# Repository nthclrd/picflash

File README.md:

# picflash

Programmeur PIC open source en Rust, pour remplacer MPLAB IPE. Il pilote une
carte maison à RP2040 (prototype sur Pi Pico en attendant le PCB) ou un PICkit
4, PICkit 5, PICkit Basic ou MPLAB Snap. Il assemble, programme et désassemble
sans MPLAB X ni XC8.

**État :** testé seulement sur un PIC simulé. Ni le PICkit, ni la carte, ni le
firmware n'ont tourné sur du vrai matériel ; la carte (`hardware/`) n'a pas été
fabriquée. Développé avec l'aide de Claude (Anthropic).

## Installer

| Système | Fichier | Remarque |
|---------|---------|----------|
| macOS   | `.dmg`  | 1er lancement : clic droit > Ouvrir (app non signée) |
| Windows | `-setup.exe` | SmartScreen : « Exécuter quand même » |
| Linux   | `.deb` ou `.AppImage` | le `.deb` installe la règle udev |

Dans la fenêtre : déposer un `.asm` ou un `.hex`, puis « Programmer ».
En ligne de commande : `cargo install --path host`.

## Utiliser

```sh
picflash asm blink.asm               # -> blink.hex
picflash write blink.hex             # efface, écrit, vérifie, lance
picflash read dump.hex
picflash -P16F1789 disasm blink.hex
picflash --tool pickit --power 3.3 id
picflash parts                       # puces supportées
picflash-ipecmd -TPSIM -E -M -P16F1789 -Fblink.hex -OL   # mêmes options qu'ipecmd
```

`-TPSIM` (ou « Simulateur » dans la fenêtre) fait tout sur un PIC simulé, sans
matériel. L'onglet « Débogueur » exécute le programme pas à pas sur ce
simulateur (sans périphériques).

Dans le `Makefile` du labo, remplacer `ipecmd` par `picflash-ipecmd` :

```make
IPECMD ?= $(HOME)/.cargo/bin/picflash-ipecmd
```

## Programmateurs

| Outil | Basse tension (LVP) | Haute tension (VPP) | Alimente la cible |
|-------|:--:|:--:|:--:|
| carte picflash | oui | oui | 1,5-4,8 V |
| prototype Pi Pico | oui | non | non |
| PICkit 4 / 5 | oui | oui | oui |
| PICkit Basic, Snap | oui | non | non |

Les outils Microchip doivent être en mode MPLAB. Windows : pilote WinUSB
installé par MPLAB X. Détails du protocole : `docs/pickit-gen4.md`.

## Puces supportées

201 PIC16 enhanced mid-range (familles PIC16F1xxx et PIC16F18xxx), décrites par
la base `host/data/devices.json.gz` extraite des device packs Microchip
(Apache-2.0). Une spec de programmation n'est ajoutée que si toutes ses puces
suivent exactement la même séquence (`SPECS` dans `host/src/device.rs`).

## Assembleur

`picflash asm` accepte les sources `pic-as` (XC8) pour PIC16 enhanced :
directives, macros, `PSECT`, `CONFIG`, `#include <xc.inc>`. Vérifié contre
`pic-as` v3.10 sur le `blink.asm` du labo et 400 programmes aléatoires : même
`.hex`, mêmes erreurs. Non supporté : PIC18, PIC10/12, plusieurs fichiers
liés, `IRP`, labels temporaires.

## Câblage du prototype Pi Pico

| Pico | PIC16F1789 (PDIP-40) | ICSP |
|------|----------------------|------|
| GP4 | MCLR (1) | 1 |
| 3V3(OUT) | VDD (11, 32) | 2 |
| GND | VSS (12, 31) | 3 |
| GP3 | ICSPDAT (40) | 4 |
| GP2 | ICSPCLK (39) | 5 |

Cible en 3,3 V. Garder `CONFIG LVP = ON` : `picflash write` refuse sinon.

Firmware : brancher en maintenant BOOTSEL, copier `picflash-firmware-pico.uf2`
(ou `picflash-firmware.uf2` pour la carte) sur le disque RPI-RP2.

## Structure

| Dossier | Rôle |
|---------|------|
| `host/` | CLI, assembleur, simulateur, programmation |
| `gui/` | interface |
| `protocol/` | protocole USB partagé hôte/firmware |
| `firmware/` | RP2040 : exécute les séquences bit à bit envoyées par l'hôte |
| `hardware/` | carte KiCad et fichiers JLCPCB |

Toute la logique PIC est côté PC : une nouvelle famille ne demande pas de
reflasher la carte.

## Tests

```sh
cargo test
```

Le PIC simulé décode chaque front d'horloge comme la vraie puce ; les tests
échouent si une séquence est fausse (ordre des bits, attente oubliée…). Ça ne
remplace pas un essai sur vraie puce.

## Licence

MIT (`LICENSE`). Données de puces (`host/data/`) : Apache-2.0, Microchip.

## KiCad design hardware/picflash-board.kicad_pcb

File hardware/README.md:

# Carte picflash (RP2040)

Design original tiré des datasheets publiques (RP2040, MT3608, TLV758,
SN74LVC1T45). **Non testé, à relire avant fabrication.**

## Générer

Le schéma et le PCB sont générés par les scripts de `tools/` : la netlist
Python (`tools/gen_schematic.py`) est la source de vérité.

```sh
make all FREEROUTING=/chemin/freerouting-2.4.1.jar
```

Étapes : schéma généré et vérifié net par net, placement, routage automatique
(Freerouting), plans de masse, ERC/DRC (0 erreur), puis `fab/` : Gerber,
perçages, BOM et CPL au format JLCPCB. Chaque pièce de la BOM a un numéro LCSC
(stock vérifié le 15/10/2026, à revérifier à la commande).

Carte 72 × 44 mm, 4 couches (In1 masse, In2 +3,3 V), composants sur une face.

## Blocs

| Bloc | Composants | Rôle |
|------|------------|------|
| USB | J1 USB-C, U2 USBLC6, F1 | alimentation 5 V, données protégées |
| 3,3 V | U3 AP2112K | logique |
| MCU | U1 RP2040, U4 flash, Y1 12 MHz | |
| Lignes ICSP | U5-U9 SN74LVC1T45 | adaptation 1,65-5,5 V, haute impédance au démarrage |
| VPP | U11 MT3608 | 6,7-13,9 V, réglé par PWM, mesuré sur ADC1 |
| VDD cible | U12 TLV75801 | 1,5-4,86 V, réglé par PWM, mesuré sur ADC0 |
| MCLR | Q1, U10 + D5, Q3 | VPP, niveau VDD ou masse |
| Connecteur | J2 8 broches | brochage PICkit 4/5 |

Brochage GPIO : `firmware/src/hw_board.rs`.

## Règles pour le firmware

- Ne jamais activer VPP_ON et MCLR_PD en même temps.
- PWM à 0 = tension max (13,9 V pour VPP) : fixer le PWM avant d'activer le
  régulateur.
- Avant d'alimenter la cible, vérifier sur ADC0 qu'aucune alimentation
  externe n'est présente.

## Avant de commander

- Relire le routage automatique : masse sous l'USB, boucle du MT3608, pistes
  VPP/MCLR.
- Vérifier les rotations du CPL dans l'aperçu JLCPCB.
- Valeurs à valider sur la première carte : self 22 µH, stabilité des
  régulateurs avec l'injection PWM.
- J2 est traversant : assemblage THT ou soudure à la main.

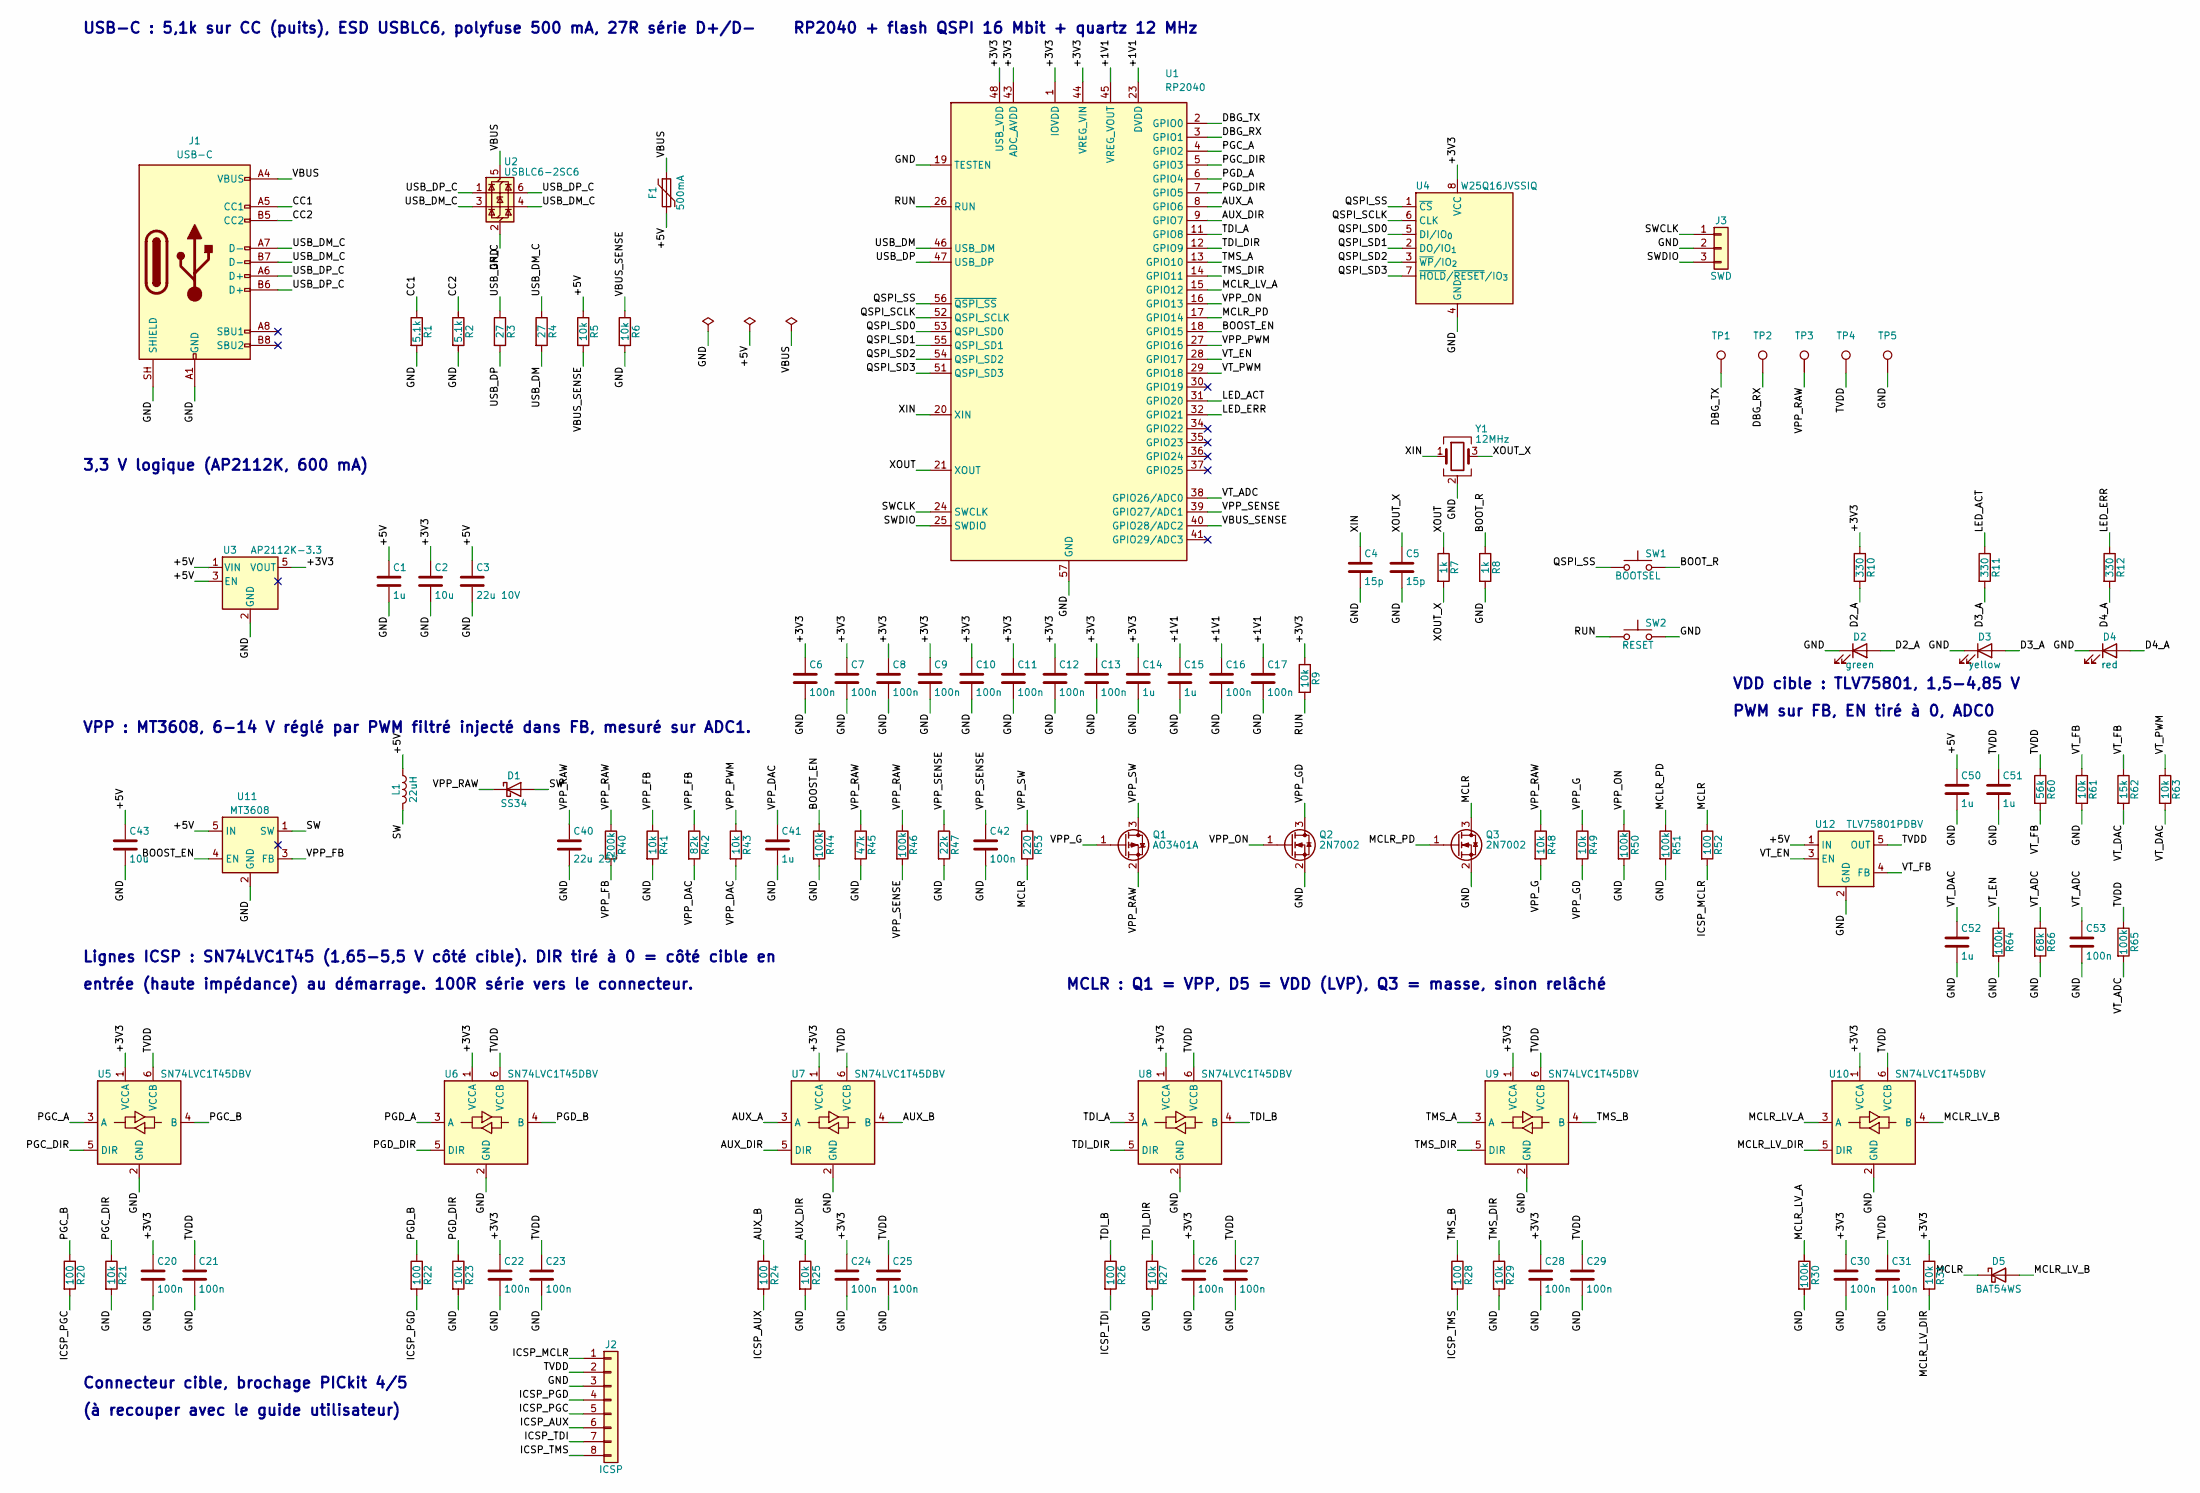
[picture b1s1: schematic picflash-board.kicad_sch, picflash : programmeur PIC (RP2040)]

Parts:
C1, C14, C15, C41, C50, C51, C52: 1u; C_0603_1608Metric; LCSC C15849
C2, C43: 10u; C_0805_2012Metric; LCSC C15850
C3: 22u 10V; C_0805_2012Metric; LCSC C45783
C4, C5: 15p; C_0603_1608Metric; LCSC C1644
C6, C7, C8, C9, C10, C11, C12, C13, C16, C17, C20, C21, C22, C23, C24, C25, C26, C27, C28, C29, C30, C31, C42, C53: 100n; C_0603_1608Metric; LCSC C14663
C40: 22u 25V; C_1206_3216Metric; LCSC C12891
D1: SS34; D_SMA; LCSC C8678
D2: green; LED_0603_1608Metric; LCSC C12624
D3: yellow; LED_0603_1608Metric; LCSC C2287
D4: red; LED_0603_1608Metric; LCSC C2286
D5: BAT54WS; D_SOD-323; LCSC C7502694
F1: 500mA; Fuse_1206_3216Metric; LCSC C720075
J1: USB-C; USB_C_Receptacle_HRO_TYPE-C-31-M-12; LCSC C165948
J2: ICSP; PinSocket_1x08_P2.54mm_Horizontal; LCSC C22436149
J3: SWD; PinHeader_1x03_P1.27mm_Vertical; LCSC C22438100
L1: 22uH; L_Cenker_CKCS4030; LCSC C354592
Q1: AO3401A; SOT-23; LCSC C15127
Q2, Q3: 2N7002; SOT-23; LCSC C8545
R1, R2: 5.1k; R_0603_1608Metric; LCSC C23186
R3, R4: 27; R_0603_1608Metric; LCSC C25190
R5, R6, R9, R21, R23, R25, R27, R29, R31, R41, R43, R48, R49, R61, R63: 10k; R_0603_1608Metric; LCSC C25804
R7, R8: 1k; R_0603_1608Metric; LCSC C21190
R10, R11, R12: 330; R_0603_1608Metric; LCSC C23138
R20, R22, R24, R26, R28, R52: 100; R_0603_1608Metric; LCSC C22775
R30, R44, R46, R50, R51, R64, R65: 100k; R_0603_1608Metric; LCSC C25803
R40: 200k; R_0603_1608Metric; LCSC C25811
R42: 82k; R_0603_1608Metric; LCSC C23254
R45: 47k; R_0603_1608Metric; LCSC C25819
R47: 22k; R_0603_1608Metric; LCSC C31850
R53: 220; R_0603_1608Metric; LCSC C22962
R60: 56k; R_0603_1608Metric; LCSC C23206
R62: 15k; R_0603_1608Metric; LCSC C22809
R66: 68k; R_0603_1608Metric; LCSC C23231
SW1: BOOTSEL; SW_SPST_PTS810; LCSC C221896
SW2: RESET; SW_SPST_PTS810; LCSC C221896
TP1: DBG_TX; TestPoint_Pad_D1.0mm
TP2: DBG_RX; TestPoint_Pad_D1.0mm
TP3: VPP_RAW; TestPoint_Pad_D1.0mm
TP4: TVDD; TestPoint_Pad_D1.0mm
TP5: GND; TestPoint_Pad_D1.0mm
U1: RP2040; QFN-56-1EP_7x7mm_P0.4mm_EP3.2x3.2mm; LCSC C2040
U2: USBLC6-2SC6; SOT-23-6; LCSC C7519
U3: AP2112K-3.3; SOT-23-5; LCSC C51118
U4: W25Q16JVSSIQ; SOIC-8_5.3x5.3mm_P1.27mm; LCSC C131025
U5, U6, U7, U8, U9, U10: SN74LVC1T45DBV; SOT-23-6; LCSC C7843
U11: MT3608; SOT-23-6; LCSC C84817
U12: TLV75801PDBV; SOT-23-5; LCSC C2877852
Y1: 12MHz; Crystal_SMD_3225-4Pin_3.2x2.5mm; LCSC C20625731

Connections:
/+1V1: C15.1, C16.1, C17.1, U1.23 (DVDD), U1.45 (VREG_VOUT), U1.50 (DVDD)
/+3V3: C2.1, C6.1, C7.1, C8.1, C9.1, C10.1, C11.1, C12.1, C13.1, C14.1, C20.1, C22.1, C24.1, C26.1, C28.1, C30.1, R9.1, R10.1, R31.1, U1.1 (IOVDD), U1.10 (IOVDD), U1.22 (IOVDD), U1.33 (IOVDD), U1.42 (IOVDD), U1.43 (ADC_AVDD), U1.44 (VREG_VIN), U1.48 (USB_VDD), U1.49 (IOVDD), U3.5 (VOUT), U4.8 (VCC), U5.1 (VCCA), U6.1 (VCCA), U7.1 (VCCA), U8.1 (VCCA), U9.1 (VCCA), U10.1 (VCCA)
/+5V: C1.1, C3.1, C43.1, C50.1, F1.2, L1.1, R5.1, U3.1 (VIN), U3.3 (EN), U11.5 (IN), U12.1 (IN)
/AUX_A: U1.8 (GPIO6), U7.3 (A)
/AUX_B: R24.1, U7.4 (B)
/AUX_DIR: R25.1, U1.9 (GPIO7), U7.5 (DIR)
/BOOST_EN: R44.1, U1.18 (GPIO15), U11.4 (EN)
/BOOT_R: R8.1, SW1.2
/CC1: J1.A5 (CC1), R1.1
/CC2: J1.B5 (CC2), R2.1
/D2_A: D2.2 (A), R10.2
/D3_A: D3.2 (A), R11.2
/D4_A: D4.2 (A), R12.2
/DBG_RX: TP2.1, U1.3 (GPIO1)
/DBG_TX: TP1.1, U1.2 (GPIO0)
/GND: C1.2, C2.2, C3.2, C4.2, C5.2, C6.2, C7.2, C8.2, C9.2, C10.2, C11.2, C12.2, C13.2, C14.2, C15.2, C16.2, C17.2, C20.2, C21.2, C22.2, C23.2, C24.2, C25.2, C26.2, C27.2, C28.2, C29.2, C30.2, C31.2, C40.2, C41.2, C42.2, C43.2, C50.2, C51.2, C52.2, C53.2, D2.1 (K), D3.1 (K), D4.1 (K), J1.A1 (GND), J1.A12 (GND), J1.B1 (GND), J1.B12 (GND), J1.SH (SHIELD), J2.3, J3.2, Q2.2 (S), Q3.2 (S), R1.2, R2.2, R6.2, R8.2, R21.2, R23.2, R25.2, R27.2, R29.2, R30.2, R41.2, R44.2, R45.2, R47.2, R50.2, R51.2, R61.2, R64.2, R66.2, SW2.2, TP5.1, U1.19 (TESTEN), U1.57 (GND), U2.2 (GND), U3.2 (GND), U4.4 (GND), U5.2 (GND), U6.2 (GND), U7.2 (GND), U8.2 (GND), U9.2 (GND), U10.2 (GND), U11.2 (GND), U12.2 (GND), Y1.2 (G), Y1.4 (G)
/ICSP_AUX: J2.6, R24.2
/ICSP_MCLR: J2.1, R52.2
/ICSP_PGC: J2.5, R20.2
/ICSP_PGD: J2.4, R22.2
/ICSP_TDI: J2.7, R26.2
/ICSP_TMS: J2.8, R28.2
/LED_ACT: R11.1, U1.31 (GPIO20)
/LED_ERR: R12.1, U1.32 (GPIO21)
/MCLR: D5.1 (K), Q3.3 (D), R52.1, R53.2
/MCLR_LV_A: R30.1, U1.15 (GPIO12), U10.3 (A)
/MCLR_LV_B: D5.2 (A), U10.4 (B)
/MCLR_LV_DIR: R31.2, U10.5 (DIR)
/MCLR_PD: Q3.1 (G), R51.1, U1.17 (GPIO14)
/PGC_A: U1.4 (GPIO2), U5.3 (A)
/PGC_B: R20.1, U5.4 (B)
/PGC_DIR: R21.1, U1.5 (GPIO3), U5.5 (DIR)
/PGD_A: U1.6 (GPIO4), U6.3 (A)
/PGD_B: R22.1, U6.4 (B)
/PGD_DIR: R23.1, U1.7 (GPIO5), U6.5 (DIR)
/QSPI_SCLK: U1.52 (QSPI_SCLK), U4.6 (CLK)
/QSPI_SD0: U1.53 (QSPI_SD0), U4.5 (DI/IO_{0})
/QSPI_SD1: U1.55 (QSPI_SD1), U4.2 (DO/IO_{1})
/QSPI_SD2: U1.54 (QSPI_SD2), U4.3 (~WP/IO_{2})
/QSPI_SD3: U1.51 (QSPI_SD3), U4.7 (~HOLD/~RESET/IO_{3})
/QSPI_SS: SW1.1, U1.56 (~QSPI_SS), U4.1 (~CS)
/RUN: R9.2, SW2.1, U1.26 (RUN)
/SW: D1.2 (A), L1.2, U11.1 (SW)
/SWCLK: J3.1, U1.24 (SWCLK)
/SWDIO: J3.3, U1.25 (SWDIO)
/TDI_A: U1.11 (GPIO8), U8.3 (A)
/TDI_B: R26.1, U8.4 (B)
/TDI_DIR: R27.1, U1.12 (GPIO9), U8.5 (DIR)
/TMS_A: U1.13 (GPIO10), U9.3 (A)
/TMS_B: R28.1, U9.4 (B)
/TMS_DIR: R29.1, U1.14 (GPIO11), U9.5 (DIR)
/TVDD: C21.1, C23.1, C25.1, C27.1, C29.1, C31.1, C51.1, J2.2, R60.1, R65.1, TP4.1, U5.6 (VCCB), U6.6 (VCCB), U7.6 (VCCB), U8.6 (VCCB), U9.6 (VCCB), U10.6 (VCCB), U12.5 (OUT)
/USB_DM: R4.2, U1.46 (USB_DM)
/USB_DM_C: J1.A7 (D-), J1.B7 (D-), R4.1, U2.3 (I/O2), U2.4 (I/O2)
/USB_DP: R3.2, U1.47 (USB_DP)
/USB_DP_C: J1.A6 (D+), J1.B6 (D+), R3.1, U2.1 (I/O1), U2.6 (I/O1)
/VBUS: F1.1, J1.A4 (VBUS), J1.A9 (VBUS), J1.B4 (VBUS), J1.B9 (VBUS), U2.5 (VBUS)
/VBUS_SENSE: R5.2, R6.1, U1.40 (GPIO28/ADC2)
/VPP_DAC: C41.1, R42.2, R43.2
/VPP_FB: R40.2, R41.1, R42.1, U11.3 (FB)
/VPP_G: Q1.1 (G), R48.2, R49.1
/VPP_GD: Q2.3 (D), R49.2
/VPP_ON: Q2.1 (G), R50.1, U1.16 (GPIO13)
/VPP_PWM: R43.1, U1.27 (GPIO16)
/VPP_RAW: C40.1, D1.1 (K), Q1.2 (S), R40.1, R45.1, R46.1, R48.1, TP3.1
/VPP_SENSE: C42.1, R46.2, R47.1, U1.39 (GPIO27/ADC1)
/VPP_SW: Q1.3 (D), R53.1
/VT_ADC: C53.1, R65.2, R66.1, U1.38 (GPIO26/ADC0)
/VT_DAC: C52.1, R62.2, R63.2
/VT_EN: R64.1, U1.28 (GPIO17), U12.3 (EN)
/VT_FB: R60.2, R61.1, R62.1, U12.4 (FB)
/VT_PWM: R63.1, U1.29 (GPIO18)
/XIN: C4.1, U1.20 (XIN), Y1.1
/XOUT: R7.1, U1.21 (XOUT)
/XOUT_X: C5.1, R7.2, Y1.3

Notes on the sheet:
USB-C : 5,1k sur CC (puits), ESD USBLC6, polyfuse 500 mA, 27R série D+/D-
3,3 V logique (AP2112K, 600 mA)
RP2040 + flash QSPI 16 Mbit + quartz 12 MHz
Lignes ICSP : SN74LVC1T45 (1,65-5,5 V côté cible). DIR tiré à 0 = côté cible en
entrée (haute impédance) au démarrage. 100R série vers le connecteur.
VPP : MT3608, 6-14 V réglé par PWM filtré injecté dans FB, mesuré sur ADC1.
MCLR : Q1 = VPP, D5 = VDD (LVP), Q3 = masse, sinon relâché
VDD cible : TLV75801, 1,5-4,85 V
PWM sur FB, EN tiré à 0, ADC0
Connecteur cible, brochage PICkit 4/5
(à recouper avec le guide utilisateur)

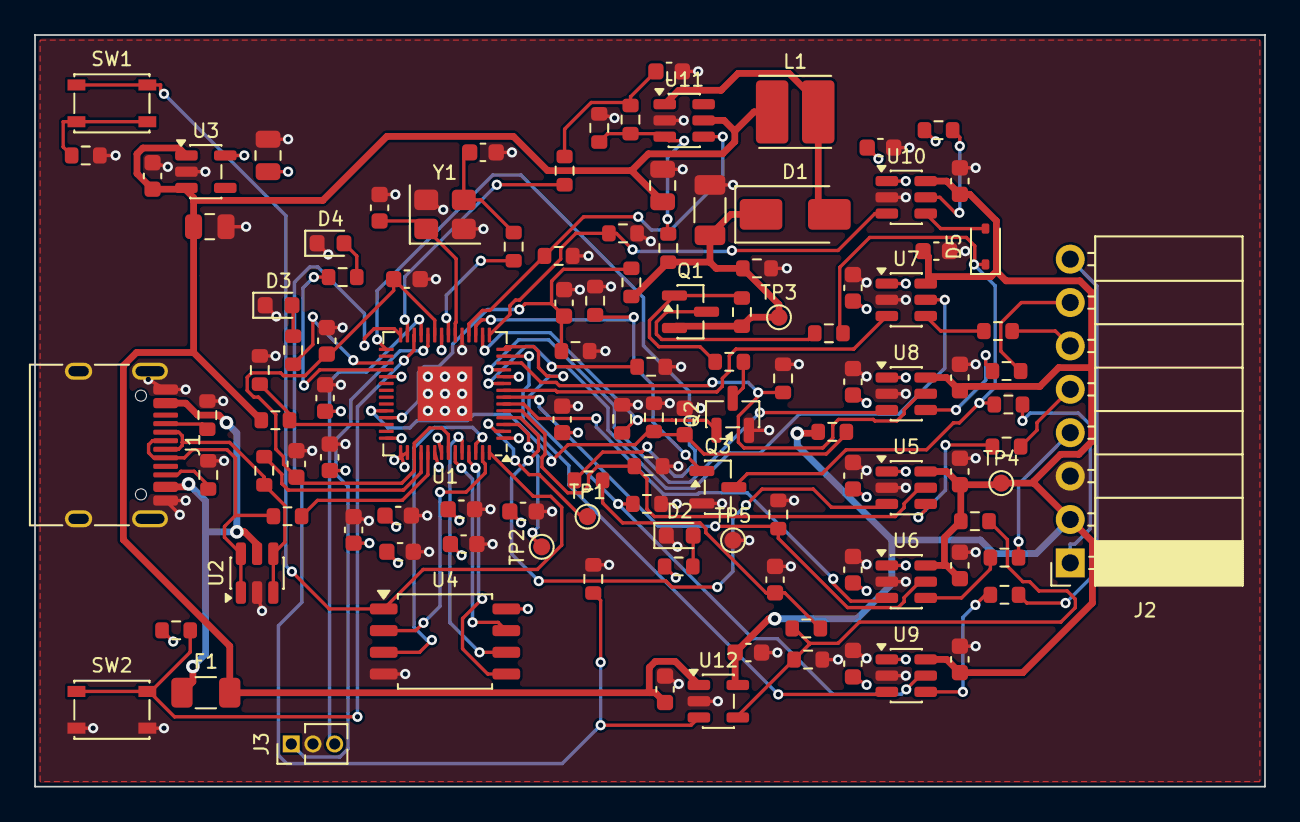
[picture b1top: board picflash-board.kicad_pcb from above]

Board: 4 copper layers, 72.0 x 44.0 mm, 115 parts (0 on the bottom side), 75 nets.

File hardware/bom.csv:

"Designator","Valeur","Empreinte","LCSC","Qté"
"C1,C14,C15,C41,C50,C51,C52","1u","Capacitor_SMD:C_0603_1608Metric","","7"
"C2","10u","Capacitor_SMD:C_0805_2012Metric","","1"
"C3","22u 10V","Capacitor_SMD:C_0805_2012Metric","","1"
"C4,C5","15p","Capacitor_SMD:C_0603_1608Metric","","2"
"C6,C7,C8,C9,C10,C11,C12,C13,C16,C17,C20,C21,C22,C23,C24,C25,C26,C27,C28,C29,C30,C31,C42,C53","100n","Capacitor_SMD:C_0603_1608Metric","","24"
"C40","22u 25V","Capacitor_SMD:C_1206_3216Metric","","1"
"D1","SS34","Diode_SMD:D_SMA","C8678","1"
"D2","green","LED_SMD:LED_0603_1608Metric","","1"
"D3","yellow","LED_SMD:LED_0603_1608Metric","","1"
"D4","red","LED_SMD:LED_0603_1608Metric","","1"
"D5","BAT54WS","Diode_SMD:D_SOD-323","","1"
"F1","500mA","Fuse:Fuse_1206_3216Metric","","1"
"J1","USB-C","Connector_USB:USB_C_Receptacle_HRO_TYPE-C-31-M-12","C165948","1"
"J2","ICSP","Connector_PinSocket_2.54mm:PinSocket_1x08_P2.54mm_Horizontal","","1"
"J3","SWD","Connector_PinHeader_1.27mm:PinHeader_1x03_P1.27mm_Vertical","","1"
"L1","22uH","Inductor_SMD:L_Cenker_CKCS4030","","1"
"Q1","AO3401A","Package_TO_SOT_SMD:SOT-23","C15127","1"
"Q2,Q3","2N7002","Package_TO_SOT_SMD:SOT-23","C8545","2"
"R1,R2","5.1k","Resistor_SMD:R_0603_1608Metric","","2"
"R3,R4","27","Resistor_SMD:R_0603_1608Metric","","2"
"R5,R6,R9,R21,R23,R25,R27,R29,R41,R43,R48,R49,R61,R63","10k","Resistor_SMD:R_0603_1608Metric","","14"
"R7,R8,R10","1k","Resistor_SMD:R_0603_1608Metric","","3"
"R11,R12","330","Resistor_SMD:R_0603_1608Metric","","2"
"R20,R22,R24,R26,R28,R52","100","Resistor_SMD:R_0603_1608Metric","","6"
"R30,R44,R46,R50,R51,R64,R65","100k","Resistor_SMD:R_0603_1608Metric","","7"
"R40","200k","Resistor_SMD:R_0603_1608Metric","","1"
"R42","82k","Resistor_SMD:R_0603_1608Metric","","1"
"R45","47k","Resistor_SMD:R_0603_1608Metric","","1"
"R47,R62","22k","Resistor_SMD:R_0603_1608Metric","","2"
"R53","220","Resistor_SMD:R_0603_1608Metric","","1"
"R60","56k","Resistor_SMD:R_0603_1608Metric","","1"
"R66","68k","Resistor_SMD:R_0603_1608Metric","","1"
"SW1","BOOTSEL","Button_Switch_SMD:SW_SPST_PTS810","","1"
"SW2","RESET","Button_Switch_SMD:SW_SPST_PTS810","","1"
"TP1","DBG_TX","TestPoint:TestPoint_Pad_D1.0mm","","1"
"TP2","DBG_RX","TestPoint:TestPoint_Pad_D1.0mm","","1"
"TP3","VPP_RAW","TestPoint:TestPoint_Pad_D1.0mm","","1"
"TP4","TVDD","TestPoint:TestPoint_Pad_D1.0mm","","1"
"TP5","GND","TestPoint:TestPoint_Pad_D1.0mm","","1"
"U1","RP2040","Package_DFN_QFN:QFN-56-1EP_7x7mm_P0.4mm_EP3.2x3.2mm","C2040","1"
"U2","USBLC6-2SC6","Package_TO_SOT_SMD:SOT-23-6","C7519","1"
"U3","AP2112K-3.3","Package_TO_SOT_SMD:SOT-23-5","C51118","1"
"U4","W25Q16JVSSIQ","Package_SO:SOIC-8_5.3x5.3mm_P1.27mm","","1"
"U5,U6,U7,U8,U9,U10","SN74LVC1T45DBV","Package_TO_SOT_SMD:SOT-23-6","","6"
"U11","MT3608","Package_TO_SOT_SMD:SOT-23-6","C84817","1"
"U12","TLV75801PDBV","Package_TO_SOT_SMD:SOT-23-5","","1"
"Y1","12MHz","Crystal:Crystal_SMD_3225-4Pin_3.2x2.5mm","C9002","1"

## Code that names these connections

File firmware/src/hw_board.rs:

//! picflash board (hardware/picflash-board.kicad_sch).
//!
//! ICSP lines go through SN74LVC1T45 shifters: DIR = 1 drives the target,
//! DIR = 0 reads it (and leaves the target side high impedance). DIR pins have
//! pull-downs, so every line is released at reset. MCLR has three drivers:
//! Q1 (VPP), U10 + D5 (VDD level) and Q3 (ground); none on = released.
//! VPP and the target supply are set by PWM "DACs" in their regulators'
//! feedback and checked on the ADC. Both regulators default to off.

use embassy_rp::adc::{self, Adc, Blocking, Channel};
use embassy_rp::gpio::{Flex, Level, Output, Pull};
use embassy_rp::pwm::{self, Pwm};
use embassy_rp::peripherals::USB;
use embassy_rp::{Peri, Peripherals};
use embassy_time::Timer;
use picflash_protocol::board::{self, Loop, VDD_LOOP, VPP_LOOP};
use picflash_protocol::{caps, status, store_bit, wire_bit, GROUP_GAP_US};

use crate::delay_us;

pub struct Hw<'d> {
    pgc: Flex<'d>,
    pgc_dir: Output<'d>,
    pgd: Flex<'d>,
    pgd_dir: Output<'d>,
    mclr_lv: Output<'d>,
    vpp_on: Output<'d>,
    mclr_pd: Output<'d>,
    boost_en: Output<'d>,
    vpp_pwm: Pwm<'d>,
    vt_en: Output<'d>,
    vt_pwm: Pwm<'d>,
    led_act: Output<'d>,
    led_err: Output<'d>,
    adc: Adc<'d, Blocking>,
    ch_tvdd: Channel<'d>,
    ch_vpp: Channel<'d>,
    vpp_ready: bool,
    vdd_on: bool,
}

fn pwm_config(duty: u16) -> pwm::Config {
    let mut c = pwm::Config::default();
    c.top = board::PWM_TOP;
    c.compare_a = duty;
    c
}

impl<'d> Hw<'d> {
    /// Takes the pins it needs and hands back the USB peripheral.
    pub fn new(p: Peripherals) -> (Self, Peri<'static, USB>) {
        let mut pgc = Flex::new(p.PIN_2);
        let mut pgd = Flex::new(p.PIN_4);
        pgc.set_as_input();
        pgd.set_as_input();
        pgd.set_pull(Pull::Down);
        let hw = Self {
            pgc,
            pgc_dir: Output::new(p.PIN_3, Level::Low),
            pgd,
            pgd_dir: Output::new(p.PIN_5, Level::Low),
            mclr_lv: Output::new(p.PIN_12, Level::Low),
            vpp_on: Output::new(p.PIN_13, Level::Low),
            mclr_pd: Output::new(p.PIN_14, Level::Low),
            boost_en: Output::new(p.PIN_15, Level::Low),
            vpp_pwm: Pwm::new_output_a(p.PWM_SLICE0, p.PIN_16, pwm_config(0)),
            vt_en: Output::new(p.PIN_17, Level::Low),
            vt_pwm: Pwm::new_output_a(p.PWM_SLICE1, p.PIN_18, pwm_config(0)),
            led_act: Output::new(p.PIN_20, Level::Low),
            led_err: Output::new(p.PIN_21, Level::Low),
            adc: Adc::new_blocking(p.ADC, adc::Config::default()),
            ch_tvdd: Channel::new_pin(p.PIN_26, Pull::None),
            ch_vpp: Channel::new_pin(p.PIN_27, Pull::None),
            vpp_ready: false,
            vdd_on: false,
        };
        (hw, p.USB)
    }

    pub fn caps(&self) -> u32 {
        caps::HIGH_VOLTAGE | caps::TARGET_POWER | caps::MEASURE
    }

    pub fn led(&mut self, active: bool, error: bool) {
        self.led_act.set_level(Level::from(active));
        self.led_err.set_level(Level::from(error));
    }

    // --- MCLR: break before make between its three drivers. ---------------
    fn mclr_off(&mut self) {
        self.vpp_on.set_low();
        self.mclr_pd.set_low();
        self.mclr_lv.set_low();
        delay_us(1);
    }
    fn mclr_low(&mut self) {
        self.mclr_off();
        self.mclr_pd.set_high();
    }
    fn mclr_vdd(&mut self) {
        self.mclr_off();
        self.mclr_lv.set_high();
    }
    fn mclr_vpp(&mut self) {
        self.mclr_off();
        self.vpp_on.set_high();
    }

    // --- Data lines: never let the RP2040 and a shifter drive A together. --
    fn drive_lines_low(&mut self) {
        self.pgc_dir.set_high();
        self.pgd_dir.set_high();
        self.pgc.set_low();
        self.pgc.set_as_output();
        self.pgd.set_low();
        self.pgd.set_as_output();
    }
    fn release_lines(&mut self) {
        self.pgc.set_as_input();
        self.pgd.set_as_input();
        self.pgc_dir.set_low();
        self.pgd_dir.set_low();
    }

    /// Lines released, MCLR at VDD: the target runs.
    pub fn release(&mut self) {
        self.release_lines();
        self.mclr_vdd();
    }

    pub fn enter(&mut self) {
        self.drive_lines_low();
        self.mclr_low();
    }

    pub fn enter_hv(&mut self) -> Result<(), u8> {
        if !self.vpp_ready {
            return Err(status::NO_VPP);
        }
        self.drive_lines_low();
        self.mclr_vpp();
        Ok(())
    }

    pub fn shift_out(&mut self, bits: u32, count: u32, msb_first: bool) {
        self.pgd_dir.set_high();
        self.pgd.set_as_output();
        for i in 0..count {
            self.pgd.set_level(Level::from(wire_bit(bits, count, msb_first, i)));
            self.pgc.set_high();
            delay_us(1);
            self.pgc.set_low();
            delay_us(1);
        }
        delay_us(GROUP_GAP_US);
    }

    pub fn shift_in(&mut self, count: u32, msb_first: bool) -> u32 {
        self.pgd.set_as_input();
        self.pgd_dir.set_low();
        delay_us(1);
        let mut value = 0;
        for i in 0..count {
            self.pgc.set_high();
            delay_us(1);
            value = store_bit(value, count, msb_first, i, self.pgd.is_high());
            self.pgc.set_low();
            delay_us(1);
        }
        delay_us(GROUP_GAP_US);
        value
    }

    // --- Analog. -----------------------------------------------------------
    fn read(&mut self, vpp: bool) -> u16 {
        let ch = if vpp { &mut self.ch_vpp } else { &mut self.ch_tvdd };
        let mut sum = 0u32;
        for _ in 0..8 {
            sum += self.adc.blocking_read(ch).unwrap_or(0) as u32;
        }
        (sum / 8) as u16
    }
    fn tvdd_mv(&mut self) -> u16 {
        board::tvdd_mv(self.read(false))
    }
    fn vpp_mv(&mut self) -> u16 {
        board::vpp_mv(self.read(true))
    }

    /// `target VDD | VPP << 16`, in mV.
    pub fn measure(&mut self) -> u32 {
        self.tvdd_mv() as u32 | (self.vpp_mv() as u32) << 16
    }

    /// Closes the loop on one regulator; `false` if it never got in range.
    async fn regulate(&mut self, vpp: bool, l: Loop, mv: u16, tolerance: i32) -> bool {
        let mut duty = l.duty_for(mv);
        for _ in 0..25 {
            let measured = if vpp { self.vpp_mv() } else { self.tvdd_mv() };
            if (measured as i32 - mv as i32).abs() <= tolerance {
                return true;
            }
            duty = l.correct(duty, measured, mv);
            if vpp {
                self.vpp_pwm.set_config(&pwm_config(duty));
            } else {
                self.vt_pwm.set_config(&pwm_config(duty));
            }
            // RC filter (10k, 1 µF): ~5 τ.
            Timer::after_millis(50).await;
        }
        false
    }

    pub async fn set_vpp(&mut self, mv: u16) -> Result<(), u8> {
        self.vpp_ready = false;
        if self.vpp_on.is_set_high() {
            self.mclr_low();
        }
        if mv == 0 {
            self.boost_en.set_low();
            return Ok(());
        }
        if !board::VPP_RANGE_MV.contains(&mv) {
            self.boost_en.set_low();
            return Err(status::VOLTAGE_RANGE);
        }
        // Set the DAC first: with PWM at 0 the boost would start at 13.9 V.
        self.vpp_pwm.set_config(&pwm_config(VPP_LOOP.duty_for(mv)));
        Timer::after_millis(60).await;
        self.boost_en.set_high();
        Timer::after_millis(10).await;
        if self.regulate(true, VPP_LOOP, mv, board::VPP_TOLERANCE_MV).await {
            self.vpp_ready = true;
            Ok(())
        } else {
            self.boost_en.set_low();
            Err(status::VPP_FAIL)
        }
    }

    pub async fn set_vdd(&mut self, mv: u16) -> Result<(), u8> {
        if mv == 0 {
            self.vt_en.set_low();
            self.vdd_on = false;
            return Ok(());
        }
        if !board::VDD_RANGE_MV.contains(&mv) {
            return Err(status::VOLTAGE_RANGE);
        }
        if !self.vdd_on && self.tvdd_mv() > board::POWERED_MV {
            return Err(status::EXTERNAL_POWER);
        }
        self.vt_pwm.set_config(&pwm_config(VDD_LOOP.duty_for(mv)));
        Timer::after_millis(60).await;
        self.vt_en.set_high();
        self.vdd_on = true;
        Timer::after_millis(5).await;
        if self.regulate(false, VDD_LOOP, mv, board::VDD_TOLERANCE_MV).await {
            Ok(())
        } else {
            self.vt_en.set_low();
            self.vdd_on = false;
            Err(status::VDD_FAIL)
        }
    }

    /// Host gone: everything off, MCLR and lines released.
    pub fn shutdown(&mut self) {
        self.mclr_off();
        self.release_lines();
        self.boost_en.set_low();
        self.vpp_ready = false;
        self.vt_en.set_low();
        self.vdd_on = false;
        self.led(false, false);
    }
}
